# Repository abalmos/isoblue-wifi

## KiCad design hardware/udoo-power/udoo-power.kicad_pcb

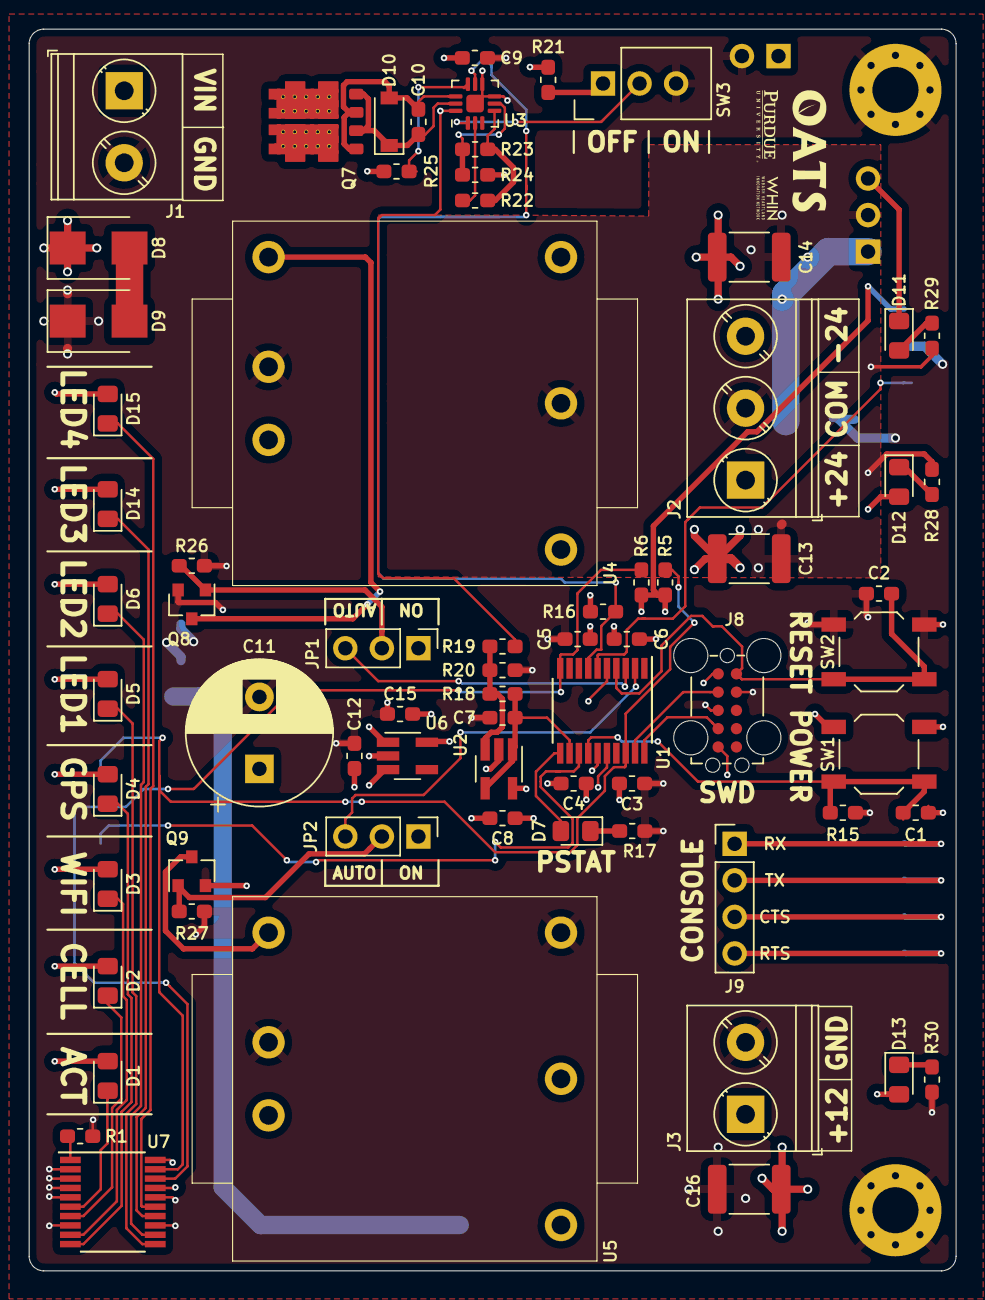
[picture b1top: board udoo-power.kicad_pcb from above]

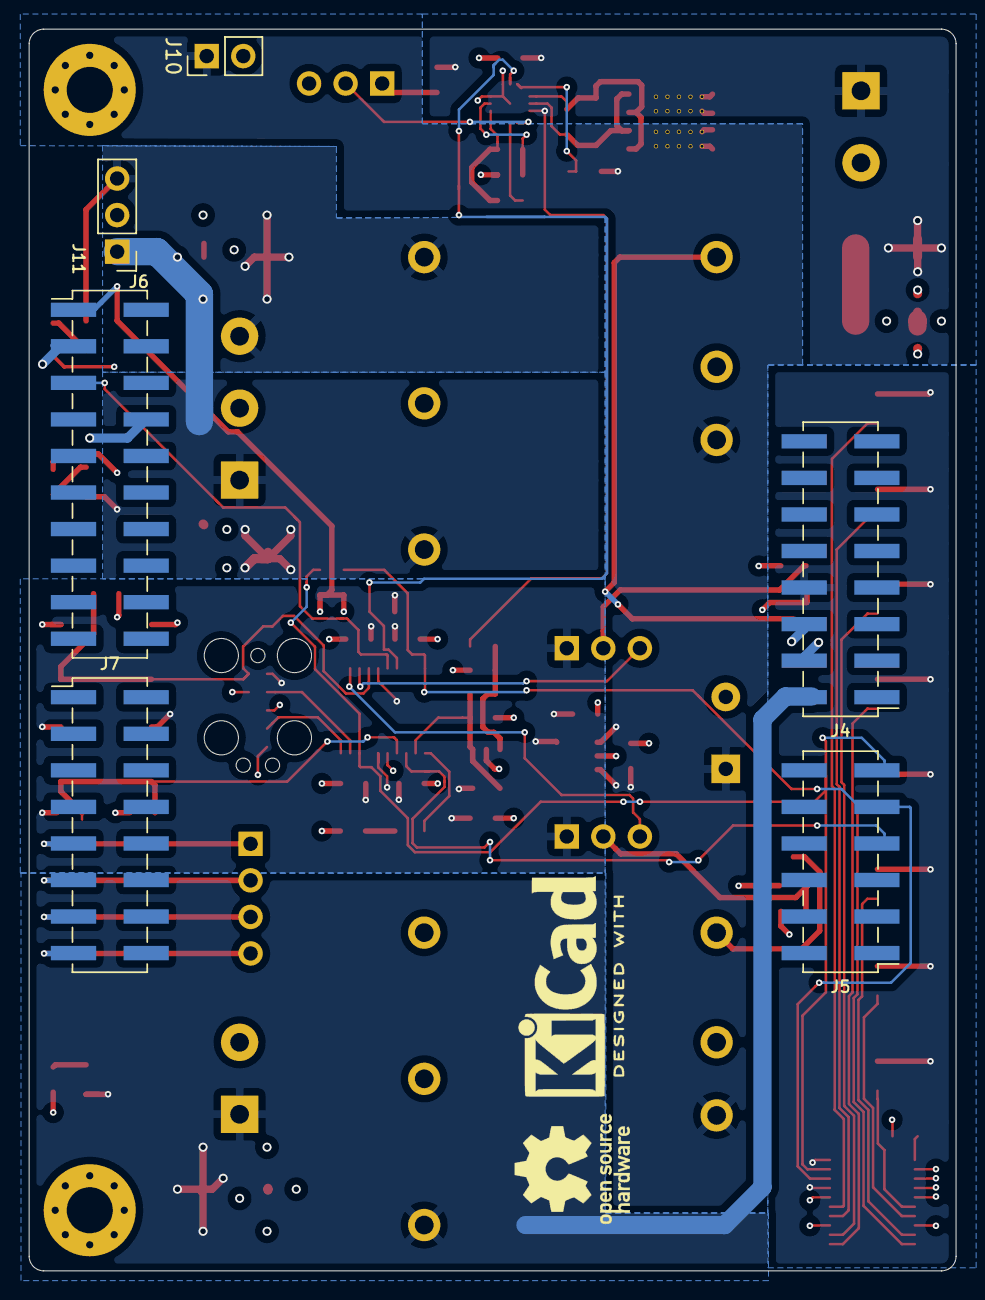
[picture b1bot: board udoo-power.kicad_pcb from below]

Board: 4 copper layers, 64.4 x 86.3 mm, 83 parts (8 on the bottom side), 54 nets.

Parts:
C1, C2, C4, C6, C7, C8, C9: 0.1uF; C_0603_1608Metric_Pad1.05x0.95mm_HandSolder
C3: 10uF; C_0603_1608Metric_Pad1.05x0.95mm_HandSolder
C5, C12: 1uF; C_0603_1608Metric_Pad1.05x0.95mm_HandSolder
C10: 10nF; C_0603_1608Metric_Pad1.05x0.95mm_HandSolder
C11: 220uF; CP_Radial_D10.0mm_P5.00mm
C13, C14, C16: 22uF; C_1812_4532Metric_Pad1.30x3.40mm_HandSolder
C15: 2.2u; C_0603_1608Metric_Pad1.05x0.95mm_HandSolder
D1: ACT.; LED_0805_2012Metric_Pad1.15x1.40mm_HandSolder
D2: CELL; LED_0805_2012Metric_Pad1.15x1.40mm_HandSolder
D3: WIFI; LED_0805_2012Metric_Pad1.15x1.40mm_HandSolder
D4: GPS; LED_0805_2012Metric_Pad1.15x1.40mm_HandSolder
D5: LED1; LED_0805_2012Metric_Pad1.15x1.40mm_HandSolder
D6: LED2; LED_0805_2012Metric_Pad1.15x1.40mm_HandSolder
D7: PC_STATUS; LED_0805_2012Metric_Pad1.15x1.40mm_HandSolder
D8: SMBJ40A; D_SMB
D9: SMBJ17A; D_SMB
D10: 18V; D_SOD-123
D11, D12, D13: REG; LED_0805_2012Metric_Pad1.15x1.40mm_HandSolder
D14: LED3; LED_0805_2012Metric_Pad1.15x1.40mm_HandSolder
D15: LED4; LED_0805_2012Metric_Pad1.15x1.40mm_HandSolder
G1: OATS_LOGO
G2: PURDUE_LOGO
G3: WHIN_LOGO
G4: KICAD_LOGO; KiCad-Logo2_6mm_SilkScreen
H1, H2: MountingHole_Pad; MountingHole_3.2mm_M3_Pad_Via
J1: Vin; TerminalBlock_Phoenix_PT-1,5-2-5.0-H_1x02_P5.00mm_Horizontal
J2: 48V_ISO; TerminalBlock_Phoenix_PT-1,5-3-5.0-H_1x03_P5.00mm_Horizontal
J3: 12V; TerminalBlock_Phoenix_PT-1,5-2-5.0-H_1x02_P5.00mm_Horizontal
J4: UDOO_CN12; PinHeader_2x08_P2.54mm_Vertical_SMD
J5: UDOO_CN14; PinHeader_2x06_P2.54mm_Vertical_SMD
J6: UDOO_CN13; PinHeader_2x10_P2.54mm_Vertical_SMD
J7: UDOO_CN15; PinHeader_2x08_P2.54mm_Vertical_SMD
J8: SWD; TC2050-IDC
J9: CONSOLE; PinHeader_1x04_P2.54mm_Vertical
J10: 12V_B2B; PinHeader_1x02_P2.54mm_Vertical
J11: 48V_ISO_B2B; PinHeader_1x03_P2.54mm_Vertical
JP1, JP2: CTRL; PinHeader_1x03_P2.54mm_Vertical
LOGO1: Logo_Open_Hardware_Small; OSHW-Logo_7.5x8mm_SilkScreen
Q7: NVMFD5C668NL; DFN-8-2EP_5x6mm_P1.27mm_EP4.84x5.55mm
Q8, Q9: BSS138; SOT-23
R1, R5, R6, R28, R29: 4.7k; R_0603_1608Metric_Pad1.05x0.95mm_HandSolder
R15, R16: 10k; R_0603_1608Metric_Pad1.05x0.95mm_HandSolder
R17: 20; R_0603_1608Metric_Pad1.05x0.95mm_HandSolder
R18: 0; R_0603_1608Metric_Pad1.05x0.95mm_HandSolder
R19: 470k; R_0603_1608Metric_Pad1.05x0.95mm_HandSolder
R20: 27k; R_0603_1608Metric_Pad1.05x0.95mm_HandSolder
R21: 100k; R_0603_1608Metric_Pad1.05x0.95mm_HandSolder
R22: 294k; R_0603_1608Metric_Pad1.05x0.95mm_HandSolder
R23: 28k; R_0603_1608Metric_Pad1.05x0.95mm_HandSolder
R24: 12.4k; R_0603_1608Metric_Pad1.05x0.95mm_HandSolder
R25: 100; R_0603_1608Metric_Pad1.05x0.95mm_HandSolder
R26, R27: 200k; R_0603_1608Metric_Pad1.05x0.95mm_HandSolder
R30: 2.4k; R_0603_1608Metric_Pad1.05x0.95mm_HandSolder
SW1: PWR; SW_SPST_TL3342
SW2: RESET; SW_SPST_TL3342
SW3: ON/OFF; ATE1D-2M3-10-Z
U1: STM32L011F4Px; TSSOP-20_4.4x6.5mm_P0.65mm
U2: TLV379; SOT-23-5_HandSoldering
U3: MAX16126; TQFN-12-EP_3x3mm_P0.5mm_EP1.23x1.23mm
U4: PDQE20-Q24-D24-D; 1x1_DC_DC_MODULE
U5: PDQ30-Q24-S12-D; 1x1_DC_DC_MODULE
U6: MIC5233; SOT-23-5_HandSoldering
U7: TLC59108xPW; TSSOP-20_4.4x6.5mm_P0.65mm

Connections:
+1V8: C1.2, C3.2, C4.2, C5.1, C6.1, C8.1, C15.1, J8.1, JP1.1, JP2.1, R16.2, SW1.2, U1.5, U1.16, U2.5, U6.5
+12V: C16.1, D13.2, J3.1, J4.2, U5.3
/12_RC: JP2.3, U1.2
/24V_COM: C13.2, C14.1, J2.2, J11.2, R28.1, R29.1, U4.4
/24_RC: JP1.3, U1.3
/+24V: C13.1, D12.2, J2.1, J11.1, U4.3
/-24V: C14.2, D11.1, J2.3, J11.3, U4.5
/CTRL_SCL: J5.9, R6.1, U1.10, U7.18
/CTRL_SDA: J5.11, R5.1, U1.18, U7.19
/FLAG: R16.1, U1.7, U3.8
/INT: J5.7, U1.13
/Power controller (PC)/NRST: C2.2, J8.10, SW2.2, U1.4
/Power controller (PC)/PWR_BTN: C1.1, R15.2, SW1.1, U1.14
/Power controller (PC)/SWCLK: J8.4, U1.20
/Power controller (PC)/SWDIO: J8.2, U1.19
/RUN: J6.5, U1.6
/Regulators (R)/12V_unreg: C11.1, C12.1, J10.1, Q7.6, R25.1, U4.1, U5.1, U6.1, U6.3
/UDOO (U)/1V8_UDOO: J6.1, R5.2, R6.2
/UDOO (U)/5V_UDOO: D1.2, D2.2, D3.2, D4.2, D5.2, D6.2, D14.2, D15.2, J4.8, U7.17, U7.20
/UDOO (U)/UART1_CTS: J7.13, J9.3
/UDOO (U)/UART1_RTS: J7.15, J9.4
/UDOO (U)/UART1_RXD: J7.9, J9.1
/UDOO (U)/UART1_TXD: J7.11, J9.2
/VIN: C9.2, D8.1, J1.1, Q7.5, R19.2, R21.2, U3.12
GND: C2.1, C3.1, C4.1, C5.2, C6.2, C7.2, C8.2, C9.1, C11.2, C12.2, C15.2, C16.2, D9.1, H1.1, H2.1, J1.2, J3.2, J4.4, J4.6, J6.3, J6.8, J8.3, J8.5, J8.9, J10.2, Q8.2, Q9.2, R1.1, R15.1, R17.1, R20.1, R24.1, R26.1, R27.1, R30.1, SW2.1, SW3.3, U1.15, U2.2, U3.6, U3.7, U3.EP, U4.2, U5.2, U5.5, U6.2, U7.2, U7.3, U7.4, U7.5, U7.8, U7.13, U7.16
unnamed: C7.1, R18.2, U1.12, U2.1, U2.4
unnamed: C10.1, D10.2, Q7.1, Q7.3, U3.10
unnamed: C10.2, D10.1, Q7.2, Q7.4, U3.11
unnamed: D1.1, U7.6
unnamed: D2.1, U7.7
unnamed: D3.1, U7.9
unnamed: D4.1, U7.10
unnamed: D5.1, U7.11
unnamed: D6.1, U7.12
unnamed: D7.1, R17.2
unnamed: D7.2, U1.11
unnamed: D8.2, D9.2
unnamed: D11.2, R29.2
unnamed: D12.1, R28.2
unnamed: D13.1, R30.2
unnamed: D14.1, U7.14
unnamed: D15.1, U7.15
unnamed: JP1.2, Q8.1, R26.2
unnamed: JP2.2, Q9.1, R27.2
unnamed: Q8.3, U4.6
unnamed: Q9.3, U5.6
unnamed: R1.2, U7.1
unnamed: R18.1, R19.1, R20.2, U2.3
unnamed: R21.1, SW3.1
unnamed: R22.1, R23.2, U3.4
unnamed: R22.2, U3.2
unnamed: R23.1, R24.2, U3.5
unnamed: R25.2, U3.9
unnamed: SW3.2, U3.1

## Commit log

2020-02-06 Initial dump (we shouldn't use this repo)
